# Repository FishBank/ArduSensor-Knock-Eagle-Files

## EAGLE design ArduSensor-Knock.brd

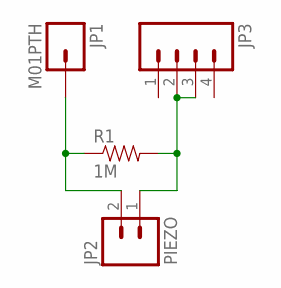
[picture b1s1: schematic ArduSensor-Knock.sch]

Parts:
JP1: M01PTH; 1X01
JP2: PIEZO; 1X02
JP3: M04PTH; 1X04
R1: 1M; AXIAL-0.3

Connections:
unnamed: JP1.1, JP2.2, R1.P$1 (1)
unnamed: JP2.1, JP3.2, JP3.3, R1.P$2 (2)

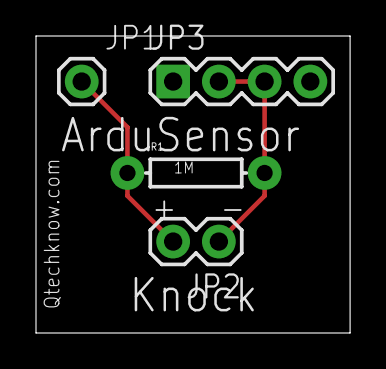
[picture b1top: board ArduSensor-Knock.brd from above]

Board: 2 copper layers, 17.5 x 16.5 mm, 4 parts (0 on the bottom side), 2 nets.

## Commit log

2012-07-13 Schematic

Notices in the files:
parts and their libraries:
SFE Connectors: Licensing: CC v3.0 Share-Alike You are welcome to use this library for commercial purposes.
